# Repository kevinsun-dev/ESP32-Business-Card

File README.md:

# ESP32 Business Card Web Server

**A 0.8mm thick PCB business card that hosts its own website.**

This repository contains the KiCad hardware design files and the PlatformIO firmware source code for a custom PCB business card. The card features a built-in ESP32-C3 microcontroller, a PCB-edge USB-C connector, and enough flash memory to host a compressed version of my personal portfolio website.

**[Read the full write-up here.](https://kevinsun.dev/blog/pcb-business-card)**

## ⚡ Features

* **Self-Hosting:** Runs a full HTTP web server directly on the card.
* **Optimized:** Uses **LittleFS** and **GZIP compression** to serve a <14kB website with minimal latency.
* **Cost-Effective:** BOM target under **$5** using the ESP32-C3FH4.

## 🛠 Hardware Design

The hardware is designed around the **Espressif ESP32-C3FH4**, a RISC-V microcontroller with built-in 4MB flash, chosen for its low component count and ease of use.

### Key Specs

* **MCU:** ESP32-C3FH4 (RISC-V, 160MHz, WiFi/BLE)
* **Connector:** [PCB-Edge USB-C](https://github.com/AnasMalas/pcb-edge-usb-c) (Reversible)
* **PCB Thickness:** 0.8mm (Critical for USB-C fit)
* **Finish:** ENIG (Electroless Nickel Immersion Gold) for durability and aesthetics.

## 💻 Firmware

The firmware is built using **PlatformIO** with the **Arduino Framework** atop **ESP-IDF**.

### Key Capabilities

* **LittleFS Filesystem:** Decouples the website content from the C++ firmware logic.
* **GZIP Compression:** All web assets are pre-compressed (gzip) to reduce transmission size (~5kB) and load times.
* **OTA Updates:** The website and firmware can be updated wirelessly without plugging the card back into a programmer.
* **Dynamic Routing:** Automatically maps URLs (e.g., `/about`) to their corresponding compressed files (`/about.html.gz`).

## 🚀 Getting Started

### 1. Build the Hardware

Generate gerbers for your PCB using the KiCad files in this repository and assemble the components listed in the BOM.

### 2. Flash the Firmware

1. Install [PlatformIO](https://platformio.org/).
2. Clone this repository.
3. Connect the board via USB (hold the BOOT button while plugging in to enter bootloader mode).
4. Upload the firmware:
```bash
pio run --target upload
```

### 3. Upload the Website

The website files live in the `data/` folder. You must upload the filesystem image separately from the code.

```bash
# Compress your site and place in data/
# Then run:
pio run --target uploadfs
```

## 🌐 Live Demo

I've set up an ESP32 webserver hosting a mirror of my website 24/7.

* **Card Site:** [https://card.kevinsun.dev](https://card.kevinsun.dev)
* **Card Status:** [https://card.kevinsun.dev/status](https://www.google.com/url?sa=E&source=gmail&q=https://card.kevinsun.dev/status) (Tunneled via Cloudflare)

## 📄 License

* **Hardware:** Creative Commons Attribution-ShareAlike 4.0 (CC BY-SA 4.0)
* **Firmware:** MIT License

## 🙌 Credits & Inspiration

* **[mitxela](https://mitxela.com/projects/stylocard):** For the original StyloCard inspiration.
* **[Anas Malas](https://github.com/AnasMalas/pcb-edge-usb-c):** For the PCB-edge USB-C footprint design.
* **Kevin Sun:** Project Creator.

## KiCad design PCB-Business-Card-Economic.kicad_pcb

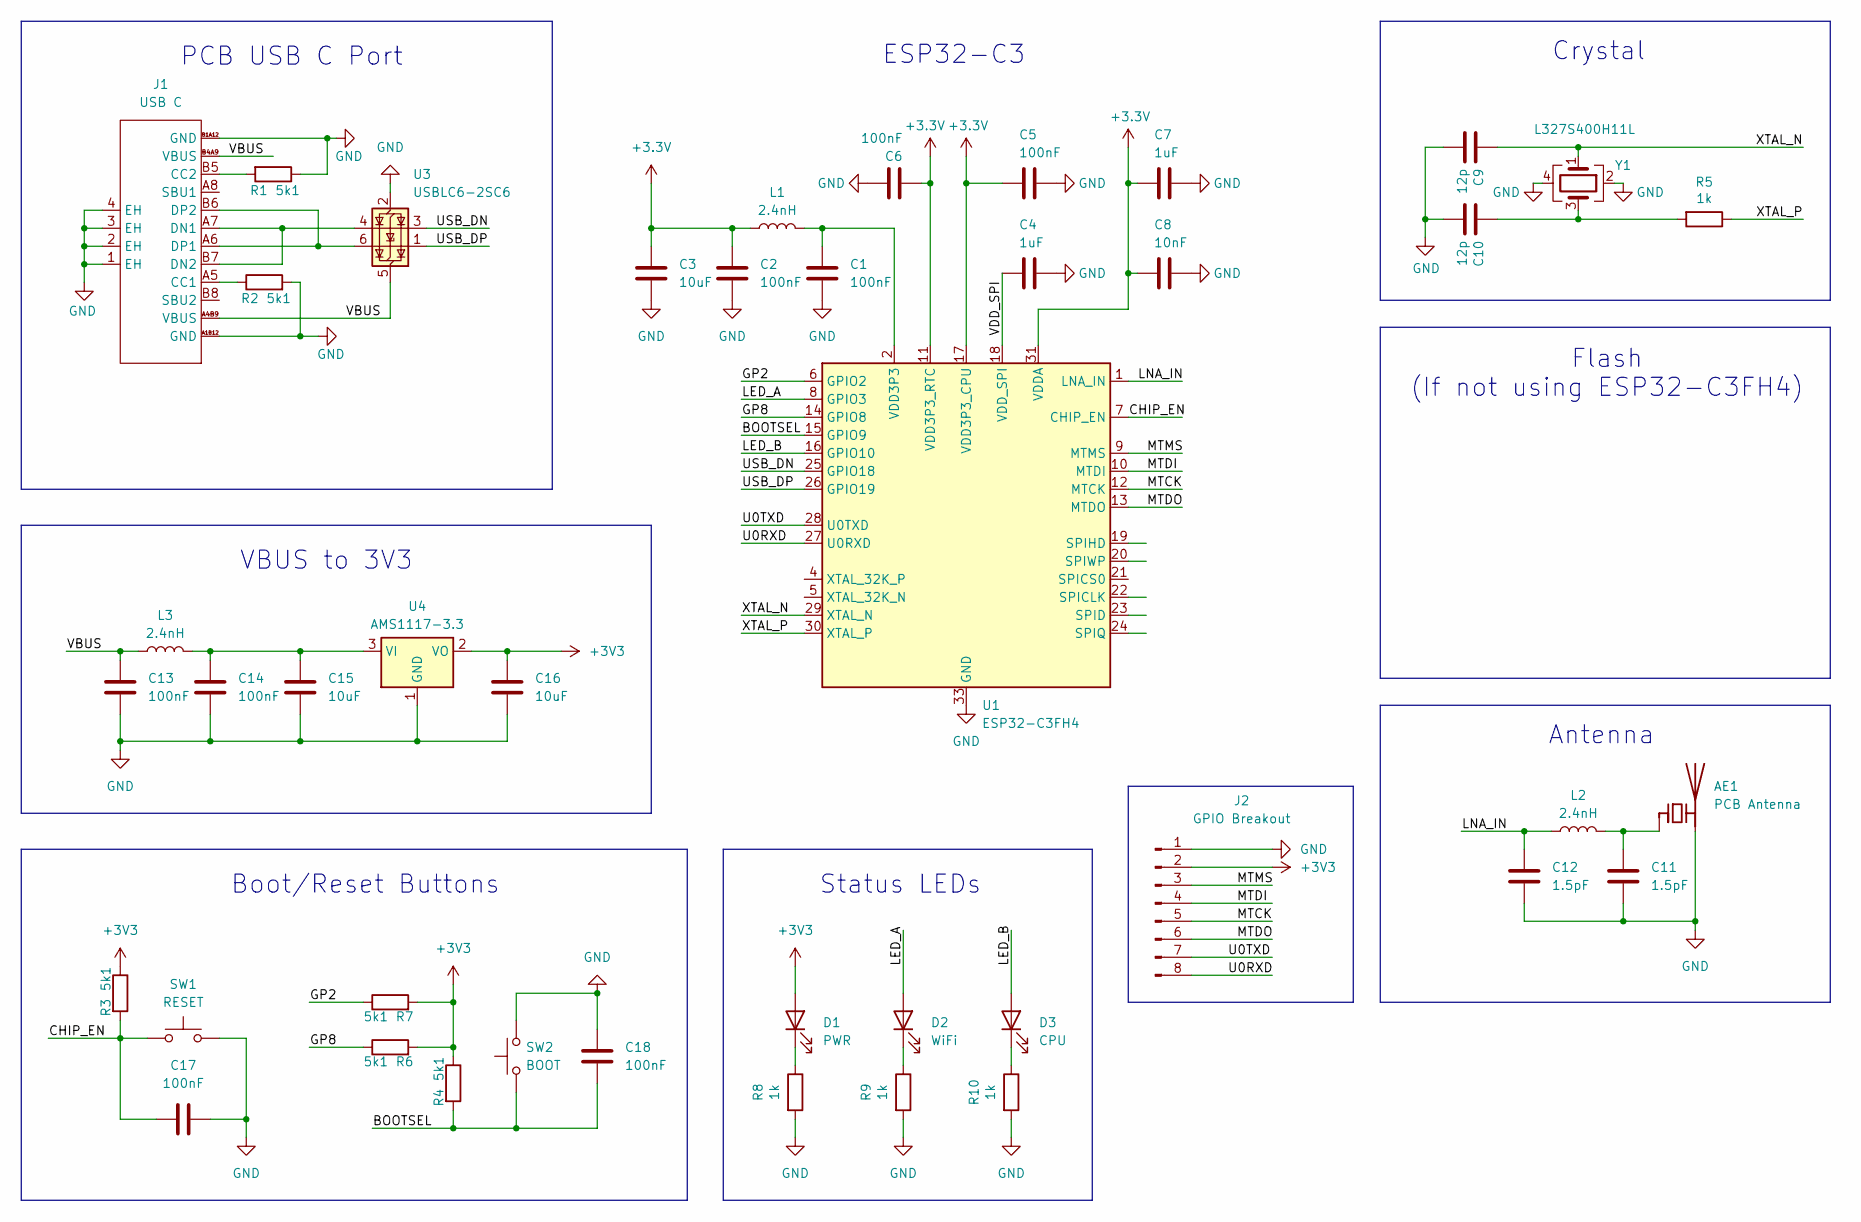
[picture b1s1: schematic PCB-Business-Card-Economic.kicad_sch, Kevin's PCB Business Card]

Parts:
AE1: PCB Antenna; pcb-antenna
C1, C2, C5, C6, C13, C14, C17, C18: 100nF; C_0402_1005Metric; JLCPCB C1525
C3, C15, C16: 10uF; C_0402_1005Metric; JLCPCB C15525
C4, C7: 1uF; C_0402_1005Metric; JLCPCB C52923
C8: 10nF; C_0402_1005Metric; JLCPCB C15195
C9, C10: 12p; C_0402_1005Metric
C11, C12: 1.5pF; C_0402_1005Metric_Pad0.74x0.62mm_HandSolder; JLCPCB C1552
D1: PWR; LED_0603_1608Metric; JLCPCB C2286
D2: WiFi; LED_0603_1608Metric; JLCPCB C2290
D3: CPU; LED_0603_1608Metric; JLCPCB C89811
J1: USB C; USB-C-SMD_TYPE-C60230-511-SC16; Manufacturer Part TYPE-C60230-511-SC16; LCSC Part Name Type-C 母 沉板
J2: GPIO Breakout; PinHeader_1x08_P2.54mm_Vertical
L1: 2.4nH; L_0402_1005Metric; JLCPCB C97997
L2, L3: 2.4nH; L_0402_1005Metric_Pad0.77x0.64mm_HandSolder; JLCPCB C97997
R1, R2, R3, R4, R6, R7: 5k1; R_0402_1005Metric; JLCPCB C25905
R5, R8, R9, R10: 1k; R_0402_1005Metric; JLCPCB C11702
SW1: RESET; SW_TS-1187A-B-A-B; JLCPCB C318884
SW2: BOOT; SW_TS-1187A-B-A-B; JLCPCB C318884
U1: ESP32-C3FH4; QFN-32-1EP_5x5mm_P0.5mm_EP3.7x3.7mm; JLCPCB C2858491
U3: USBLC6-2SC6; SOT-23-6; JLCPCB C2687116
U4: AMS1117-3.3; SOT-223-3_TabPin2; JLCPCB C6186
Y1: L327S400H11L; Crystal_SMD_3225-4Pin_3.2x2.5mm; JLCPCB C5261245

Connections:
+3.3V: C2.1, C3.1, C5.1, C6.1, C7.1, C8.1, L1.1, U1.11 (VDD3P3_RTC), U1.17 (VDD3P3_CPU), U1.31 (VDDA), U1.32 (VDDA)
+3V3: C16.1, D1.2 (A), J2.2, R3.1, R4.1, R6.2, R7.2, U4.2 (VO)
/BOOTSEL: C18.1, R4.2, SW2.1, U1.15 (GPIO9); also elsewhere on the board
/CHIP_EN: C17.1, R3.2, SW1.1, U1.7 (CHIP_EN); also elsewhere on the board
/GP2: R7.1, U1.6 (GPIO2)
/GP8: R6.1, U1.14 (GPIO8)
/LED_A: D2.2 (A), U1.8 (GPIO3)
/LED_B: D3.2 (A), U1.16 (GPIO10)
/LNA_IN: C12.1, L2.1, U1.1 (LNA_IN)
/MTCK: J2.5, U1.12 (MTCK)
/MTDI: J2.4, U1.10 (MTDI)
/MTDO: J2.6, U1.13 (MTDO)
/MTMS: J2.3, U1.9 (MTMS)
/U0RXD: J2.8, U1.27 (U0RXD)
/U0TXD: J2.7, U1.28 (U0TXD)
/USB_DN: U1.25 (GPIO18), U3.3 (I/O2)
/USB_DP: U1.26 (GPIO19), U3.1 (I/O1)
/VBUS: C13.1, J1.A4B9 (VBUS), J1.B4A9 (VBUS), L3.1, U3.5 (VBUS)
/VDD_SPI: C4.1, U1.18 (VDD_SPI)
/XTAL_N: C9.1, U1.29 (XTAL_N), Y1.1
/XTAL_P: R5.1, U1.30 (XTAL_P)
GND: AE1.2 (PCB_Trace), C1.2, C2.2, C3.2, C4.2, C5.2, C6.2, C7.2, C8.2, C9.2, C10.2, C11.2, C12.2, C13.2, C14.2, C15.2, C16.2, C17.2, C18.2, J1.1 (EH), J1.2 (EH), J1.3 (EH), J1.4 (EH), J1.A1B12 (GND), J1.B1A12 (GND), J2.1, R1.1, R2.2, R8.2, R9.2, R10.2, SW1.2, SW2.2, U1.33 (GND), U3.2 (GND), U4.1 (GND), Y1.2, Y1.4; also elsewhere on the board
unnamed 22: AE1.1 (FEED), C11.1, L2.2; also elsewhere on the board
unnamed: C1.1, L1.2, U1.2 (VDD3P3), U1.3 (VDD3P3)
unnamed: C10.1, R5.2, Y1.3
unnamed: D1.1 (K), R8.1
unnamed: D2.1 (K), R9.1
unnamed: D3.1 (K), R10.1
unnamed: J1.A5 (CC1), R2.1
unnamed: J1.B5 (CC2), R1.2
unnamed: J1.A7 (DN1), J1.B7 (DN2), U3.4 (I/O2)
unnamed: J1.A6 (DP1), J1.B6 (DP2), U3.6 (I/O1)
unnamed: C14.1, C15.1, L3.2, U4.3 (VI)

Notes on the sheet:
Flash (If not using ESP32-C3FH4)
ESP32-C3
VBUS to 3V3
Crystal
Boot/Reset Buttons
PCB USB C Port
Status LEDs
Antenna

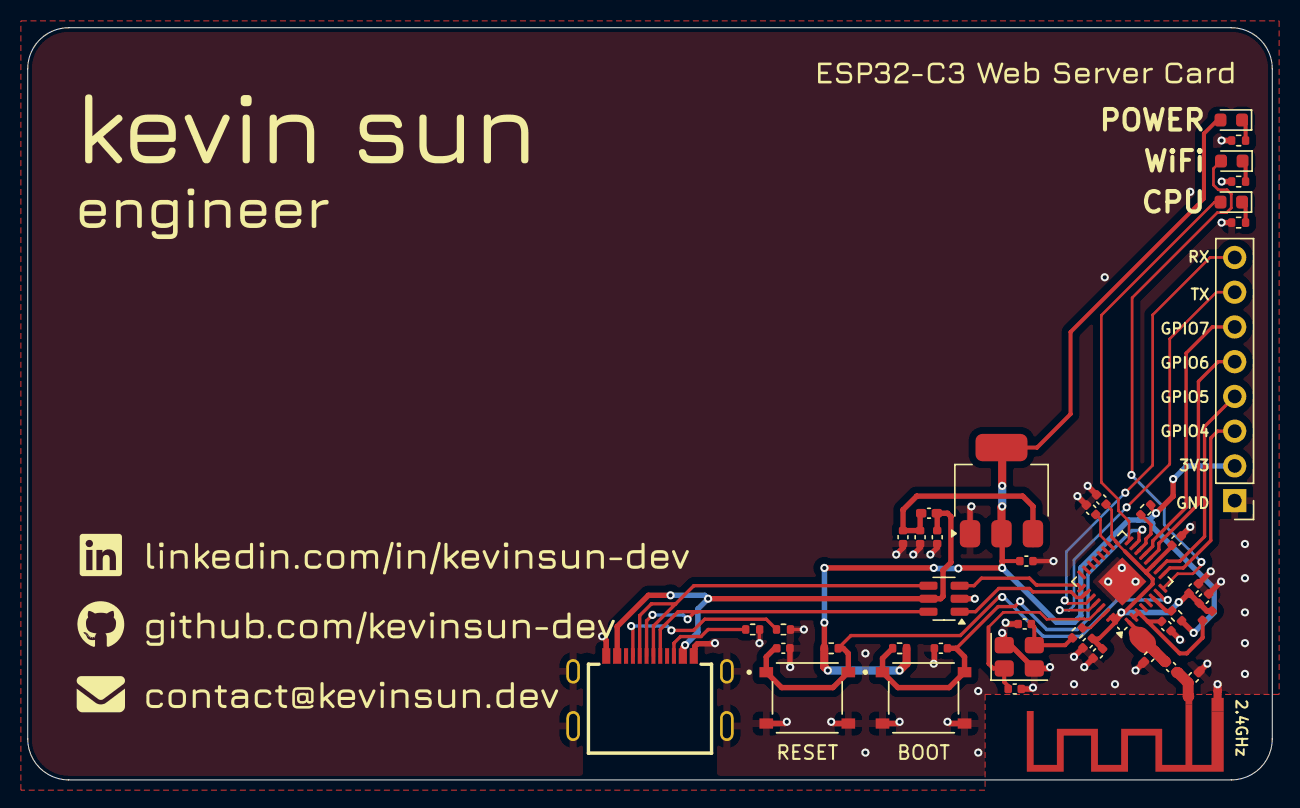
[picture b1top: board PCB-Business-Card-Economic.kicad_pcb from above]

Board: 2 copper layers, 91.0 x 55.0 mm, 43 parts (0 on the bottom side), 33 nets.

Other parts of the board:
2.4GHz: PCB Antenna; pcb-antenna
BOOT: BOOT; SW_TS-1187A-B-A-B
RESET: RESET; SW_TS-1187A-B-A-B

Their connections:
/BOOTSEL: BOOT.1; also elsewhere on the board
/CHIP_EN: RESET.1; also elsewhere on the board
GND: 2.4GHz.2 (PCB_Trace), BOOT.2, RESET.2; also elsewhere on the board
unnamed 22: 2.4GHz.1 (FEED); also elsewhere on the board

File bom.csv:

Comment,Designator,Footprint,LCSC
USBLC6-2SC6,U3,Package_TO_SOT_SMD:SOT-23-6,
BOOT,SW2,TS-1187A-B-A-B:SW_TS-1187A-B-A-B,
5k1,"R1,R2,R3,R4,R6,R7",Resistor_SMD:R_0402_1005Metric,
100nF,"C1,C2,C5,C6,C13,C14,C17,C18,C20",Capacitor_SMD:C_0402_1005Metric,
GPIO Breakout,J2,Connector_PinHeader_2.54mm:PinHeader_1x08_P2.54mm_Vertical,
10nF,C8,Capacitor_SMD:C_0402_1005Metric,
CPU,D3,LED_SMD:LED_0603_1608Metric,
1.5pF,"C11,C12",Capacitor_SMD:C_0402_1005Metric_Pad0.74x0.62mm_HandSolder,
AMS1117-3.3,U4,Package_TO_SOT_SMD:SOT-223-3_TabPin2,
2.4nH,L1,Inductor_SMD:L_0402_1005Metric,
2.4nH,"L2,L3",Inductor_SMD:L_0402_1005Metric_Pad0.77x0.64mm_HandSolder,
WiFi,D2,LED_SMD:LED_0603_1608Metric,
12p,"C9,C10",Capacitor_SMD:C_0402_1005Metric,
RESET,SW1,TS-1187A-B-A-B:SW_TS-1187A-B-A-B,
L327S400H11L,Y1,Crystal:Crystal_SMD_3225-4Pin_3.2x2.5mm,
1k,"R5,R8,R9,R10",Resistor_SMD:R_0402_1005Metric,
10uF,"C3,C15,C16",Capacitor_SMD:C_0402_1005Metric,
150pF,C19,Capacitor_SMD:C_0402_1005Metric_Pad0.74x0.62mm_HandSolder,
1uF,"C4,C7",Capacitor_SMD:C_0402_1005Metric,
PWR,D1,LED_SMD:LED_0603_1608Metric,
ESP32-C3FH4,U1,Package_DFN_QFN:QFN-32-1EP_5x5mm_P0.5mm_EP3.7x3.7mm,
NT3H2111W0FHKH,U2,C710403:C710403,

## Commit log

2025-11-09 Wrote new Edge Cuts
2025-11-09 Working Panel (does not satisfy JLCPCB economic assembly reqs)
2025-11-10 Improved Solder Mask Margin
2025-11-10 Added Economic PCB option
2025-11-18 Final Tapeout Version
2026-01-04 Added README and firmware
2026-01-04 Update README.md
    Fixed AI hallucinations
